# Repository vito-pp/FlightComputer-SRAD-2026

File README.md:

# FlightComputer-SRAD-2026

---

# RP2040 Firmware Build Instructions

This project uses the Raspberry Pi Pico SDK with CMake and the ARM GCC toolchain.

Follow these steps to set up the build environment.

---

## 1. Install dependencies (Linux)

On Debian/Ubuntu:

```bash
sudo apt update
sudo apt install cmake gcc-arm-none-eabi libnewlib-arm-none-eabi build-essential git
```

On Fedora:

```bash
sudo dnf install cmake arm-none-eabi-gcc-cs arm-none-eabi-newlib make git
```

Check installation:

```bash
arm-none-eabi-gcc --version
cmake --version
```

---

## 2. Download the Pico SDK

Clone the SDK somewhere on your system (outside this repo):

```bash
git clone https://github.com/raspberrypi/pico-sdk.git ~/pico-sdk
```

---

## 3. Set the SDK path environment variable

Set this variable so CMake can find the SDK:

```bash
export PICO_SDK_PATH=~/pico-sdk
```

To make it permanent (bash):

```bash
echo 'export PICO_SDK_PATH=~/pico-sdk' >> ~/.bashrc
source ~/.bashrc
```

---

## 4. Build the project

From the `code/` directory:

```bash
mkdir build
cd build
cmake ..
make -j$(nproc)
```

After building, the firmware file will be generated:

```bash
flight_computer.uf2
```

---

## 5. Flash to the RP2040

1. Hold the **BOOTSEL** button on the Pico
2. Plug the Pico into USB
3. Release BOOTSEL
4. Copy the UF2 file:

```bash
cp flight_computer.uf2 /media/$USER/RPI-RP2/
```

(The mount path may vary depending on your system.)

---

## 6. Rebuilding later

After the first build, you usually only need:

```bash
cd code/build
make -j$(nproc)
```

If you change `CMakeLists.txt`, run:

```bash
cmake ..
```

If something breaks, clean build:

```bash
cd code
rm -rf build
mkdir build
cd build
cmake ..
make -j$(nproc)
```

## Submodules / External Libraries

This project uses the SD-card library `no-OS-FatFS-SD-SDIO-SPI-RPi-Pico` as a Git submodule.

### Fresh clone

Clone with submodules:

```bash
git clone --recurse-submodules <repo-url>
```

### Existing clone

If the repository was already cloned without submodules:

```bash
git submodule update --init --recursive
```

After pulling updates:

```bash
git pull --recurse-submodules
git submodule update --init --recursive
```

### SD-card library notes

This project uses:

```text
no-OS-FatFS-SD-SDIO-SPI-RPi-Pico
```

in SDIO/PIO 4-bit mode.

The library contains a project-specific patch because the SD clock pin is routed differently on this board.

SD pin mapping:

```text
SD_CMD  -> GPIO18
SD_DAT0 -> GPIO19
SD_DAT1 -> GPIO20
SD_DAT2 -> GPIO21
SD_DAT3 -> GPIO22
SD_CLK  -> GPIO25
```

The SDIO PIO configuration was modified with:

```text
SDIO_CLK_PIN_D0_OFFSET = 6
```

The patched submodule commit must be available from the configured submodule remote.

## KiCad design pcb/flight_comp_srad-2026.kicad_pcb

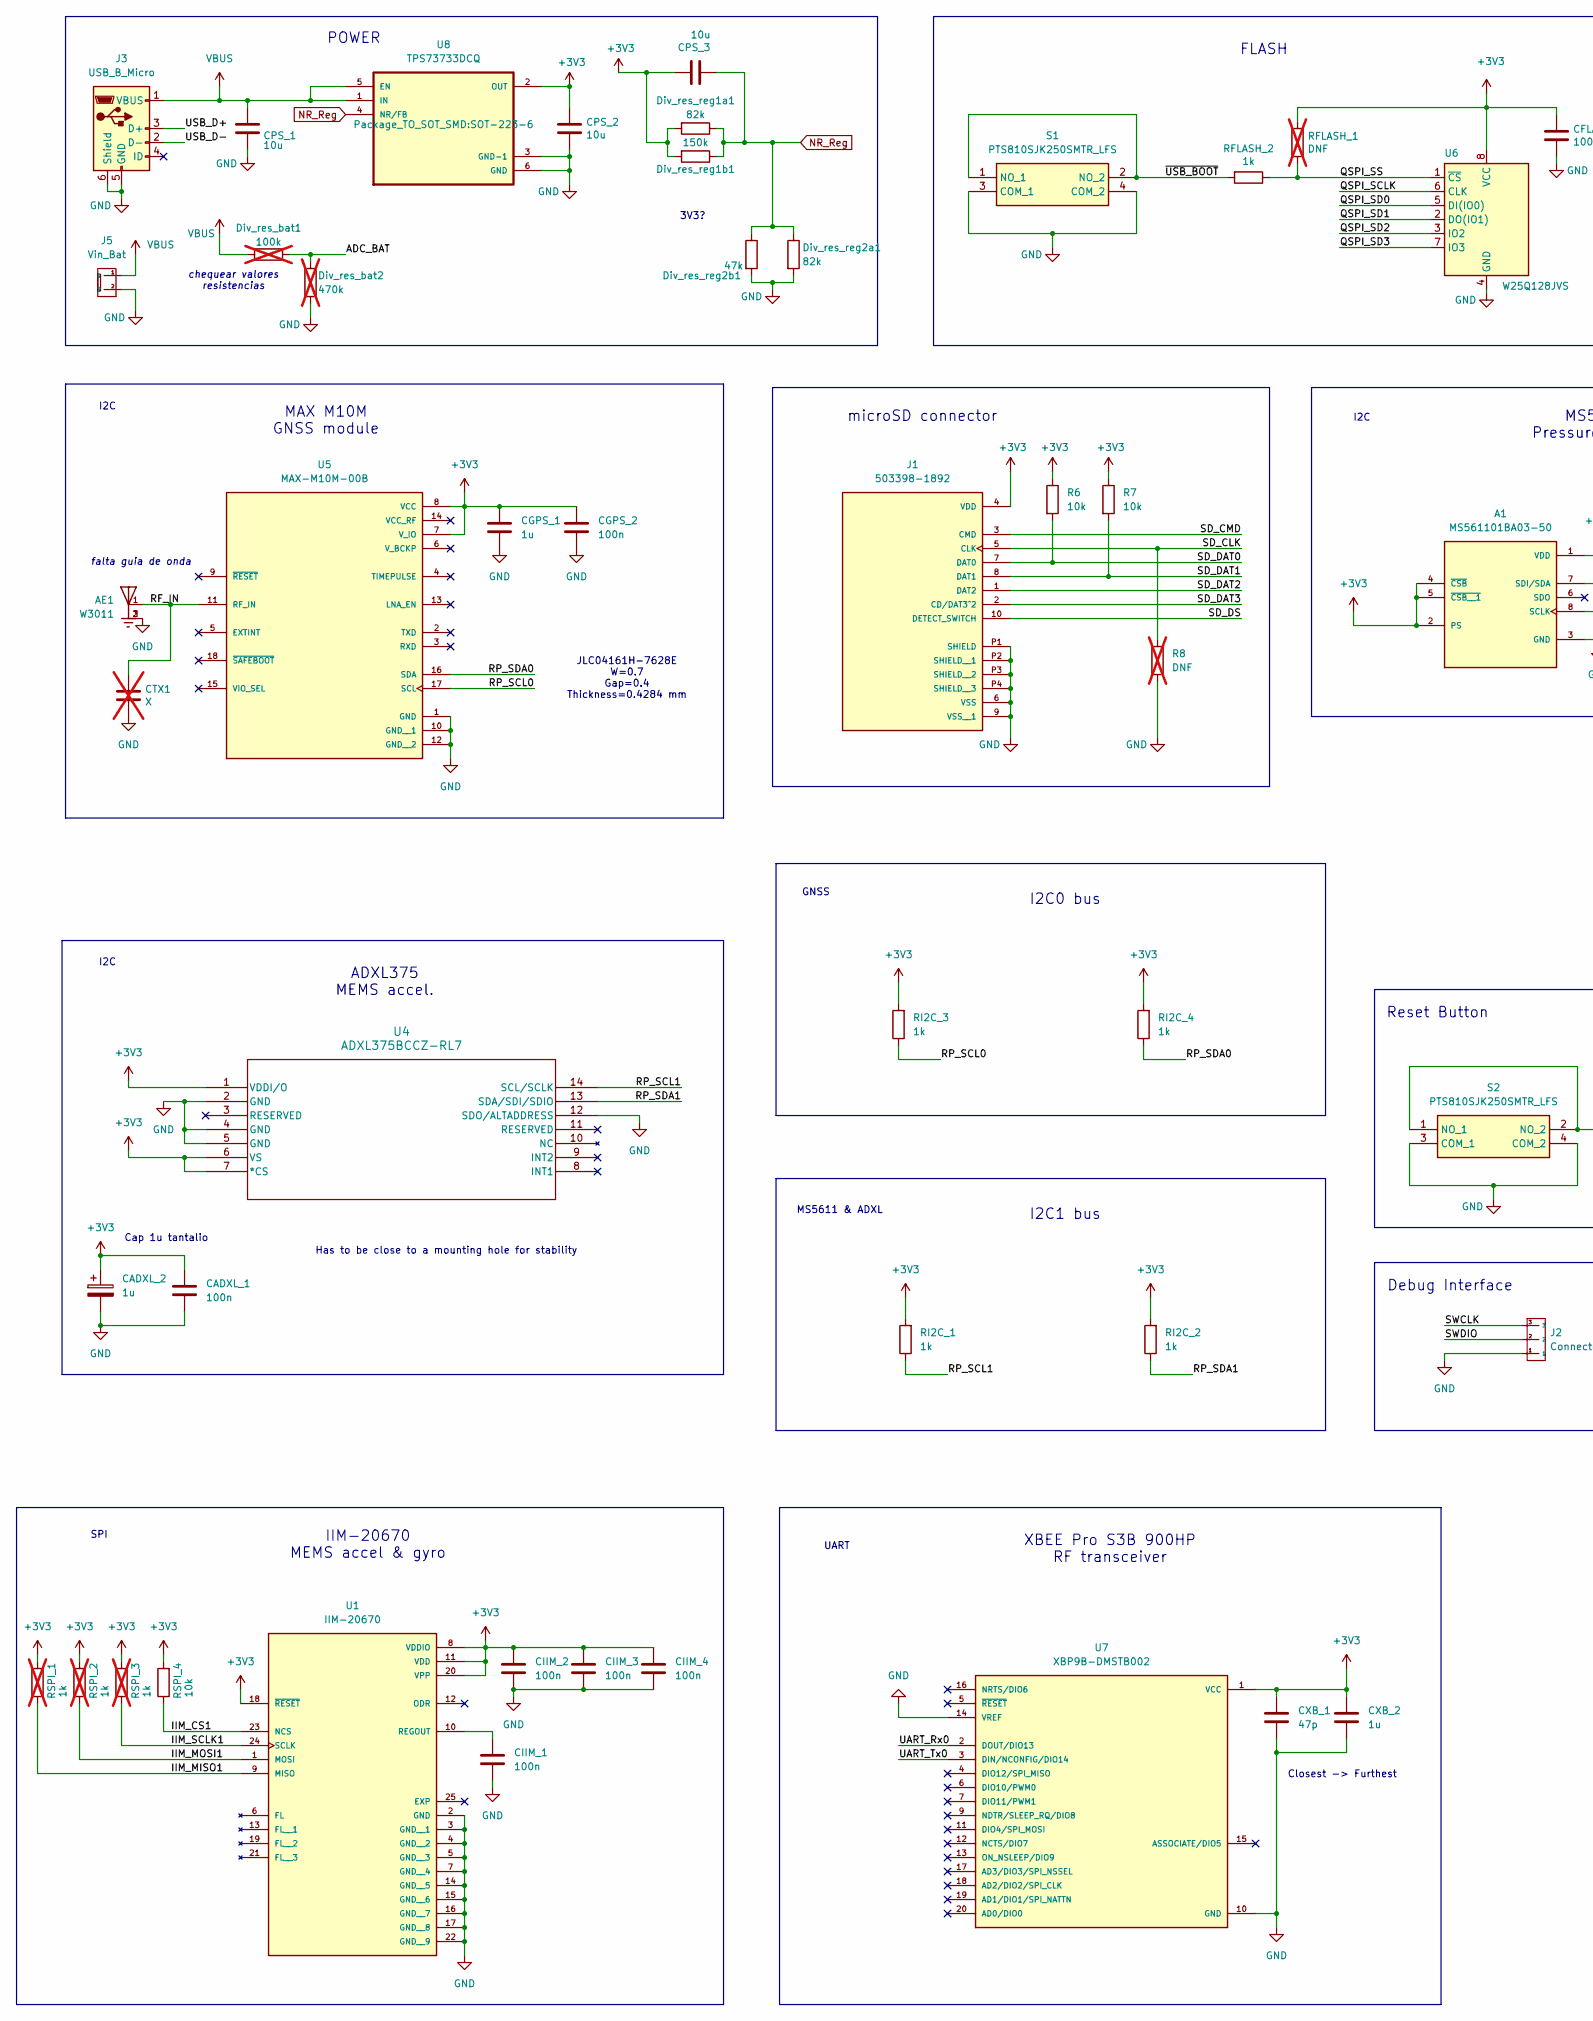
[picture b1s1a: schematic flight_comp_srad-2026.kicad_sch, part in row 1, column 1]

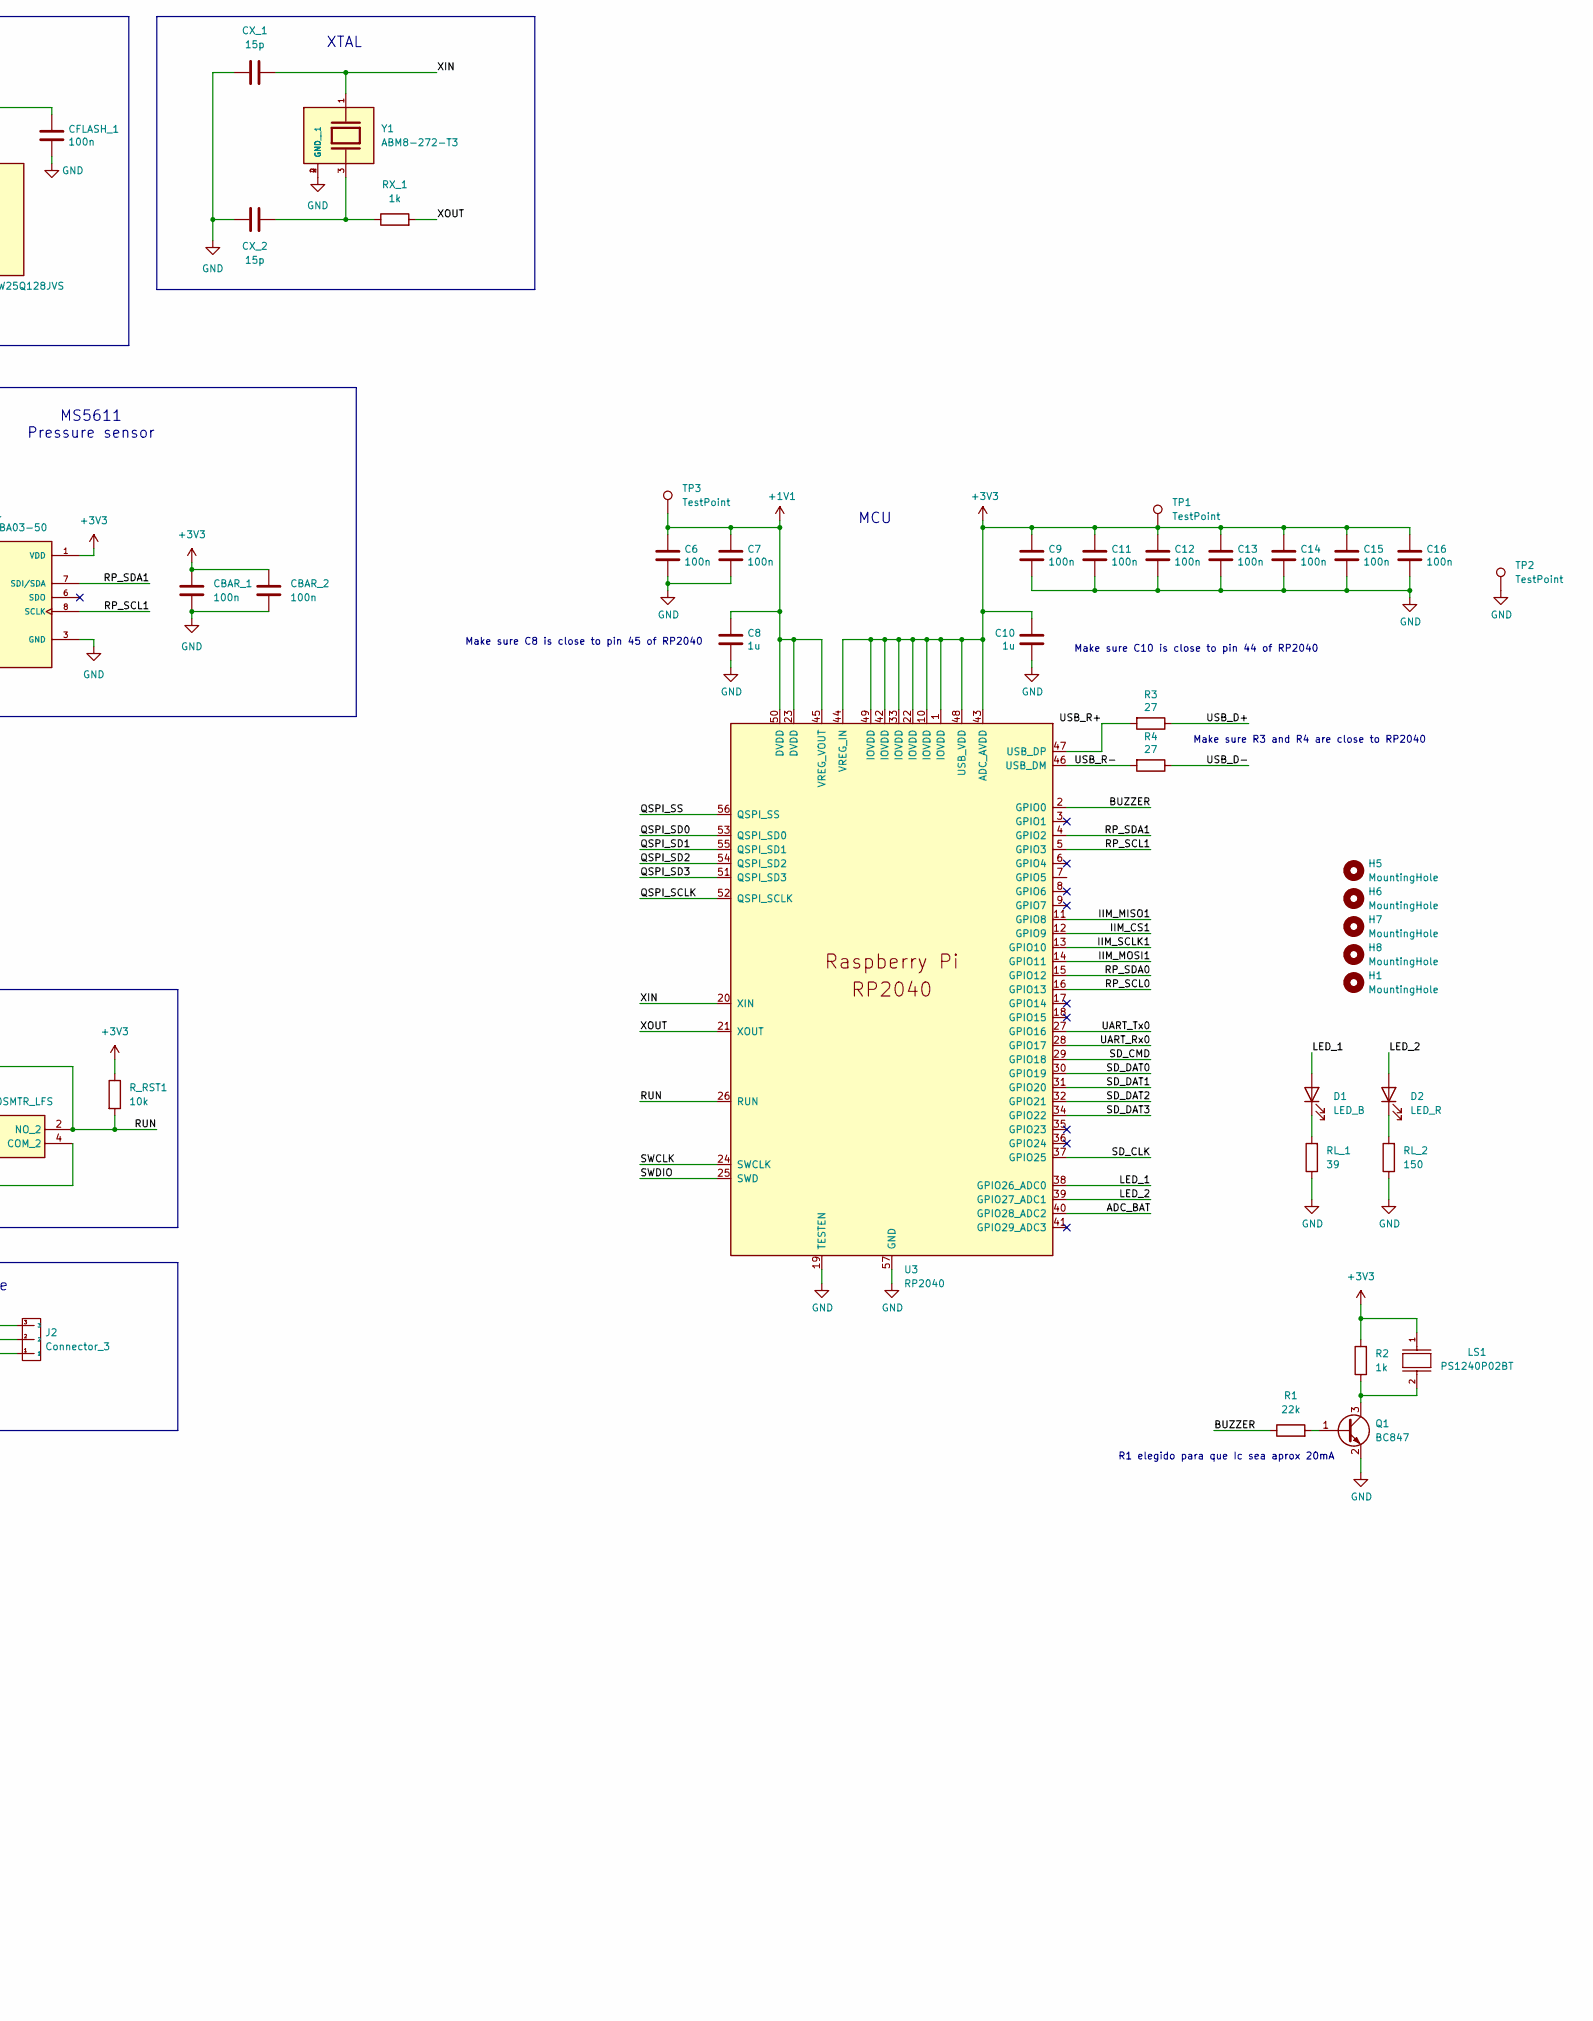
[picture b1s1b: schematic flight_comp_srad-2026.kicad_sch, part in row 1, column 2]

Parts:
A1: MS561101BA03-50; XDCR_MS561101BA03-50; PARTREV 06/2017
AE1: W3011; XDCR_W3011; PARTREV N/A
C6, C7, C9, C11, C12, C13, C14, C15, C16: 100n; C_0402_1005Metric
C8, C10: 1u; C_0402_1005Metric
CADXL_1: 100n; C_0402_1005Metric
CADXL_2: 1u; C_0805_2012Metric
CBAR_1, CBAR_2: 100n; C_0402_1005Metric
CFLASH_1: 100n; C_0402_1005Metric
CGPS_1: 1u; C_0805_2012Metric
CGPS_2: 100n; C_0603_1608Metric
CIIM_1, CIIM_2, CIIM_3, CIIM_4: 100n; C_0402_1005Metric
CPS_1, CPS_2, CPS_3: 10u; C_0805_2012Metric
CTX1: X; C_0805_2012Metric; not fitted
CXB_1: 47p; C_0805_2012Metric
CXB_2: 1u; C_0805_2012Metric
CX_1, CX_2: 15p; C_0805_2012Metric
D1: LED_B; LED_0603_1608Metric
D2: LED_R; LED_0603_1608Metric
Div_res_bat1: 100k; R_0805_2012Metric; not fitted
Div_res_bat2: 470k; R_0805_2012Metric; not fitted
Div_res_reg1a1, Div_res_reg2a1: 82k; R_0805_2012Metric
Div_res_reg1b1: 150k; R_0805_2012Metric
Div_res_reg2b1: 47k; R_0805_2012Metric
H1, H5, H6, H7, H8: MountingHole; MountingHole_3mm
J1: 503398-1892; MOLEX_503398-1892; PARTREV 0
J2: Connector_3; PinHeader_1x03_P2.54mm_Vertical
J3: USB_B_Micro; USB_Micro-B_Amphenol_10103594-0001LF_Horizontal
J5: Vin_Bat; Molex_1x02_P2.54mm
LS1: PS1240P02BT; Buzzer_TDK_PS1240P02BT_D12.2mm_H6.5mm
Q1: BC847; SOT-23
R1: 22k; R_0805_2012Metric
R2: 1k; R_0805_2012Metric
R3, R4: 27; R_0603_1608Metric
R6, R7: 10k; R_0805_2012Metric
R8: DNF; R_0805_2012Metric; not fitted
RFLASH_1: DNF; R_0805_2012Metric; not fitted
RFLASH_2: 1k; R_0805_2012Metric
RI2C_1, RI2C_2, RI2C_3, RI2C_4: 1k; R_0603_1608Metric
RL_1: 39; R_0805_2012Metric
RL_2: 150; R_0805_2012Metric
RSPI_1, RSPI_2, RSPI_3: 1k; R_0603_1608Metric; not fitted
RSPI_4: 10k; R_0603_1608Metric
RX_1: 1k; R_0805_2012Metric
R_RST1: 10k; R_0805_2012Metric
S1, S2: PTS810SJK250SMTR_LFS; PTS810SJK250SMTRLFS; Mouser Part Number 611-PTS810SJK250SMTR
TP1, TP2, TP3: TestPoint; TestPoint_Pad_D1.0mm
U1: IIM-20670; QFN50P450X450X115-25N; PARTREV 1.1
U3: RP2040; QFN-56-1EP_7x7mm_P0.4mm_EP3.2x3.2mm_ThermalVias
U4: ADXL375BCCZ-RL7; LGA-14_3x5mm_P0.8mm_LayoutBorder1x6y
U5: MAX-M10M-00B; XCVR_MAX-M10M-00B; PARTREV C1
U6: W25Q128JVS; SOIC-8_5.3x5.3mm_P1.27mm
U7: XBP9B-DMSTB002; XBEEPRO
U8: TPS73733DCQ; SOT-223-6
Y1: ABM8-272-T3; XTAL_ABM8-272-T3; PARTREV 07-29-20

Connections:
+1V1: C6.1, C7.1, C8.1, TP3.1, U3.23 (DVDD), U3.45 (VREG_VOUT), U3.50 (DVDD)
+3V3: A1.1 (VDD), A1.2 (PS), A1.4 (~CSB), A1.5 (~CSB__1), C9.1, C10.1, C11.1, C12.1, C13.1, C14.1, C15.1, C16.1, CADXL_1.1, CADXL_2.1, CBAR_1.1, CBAR_2.1, CFLASH_1.1, CGPS_1.1, CGPS_2.1, CIIM_2.1, CIIM_3.1, CIIM_4.1, CPS_2.1, CPS_3.1, CXB_1.1, CXB_2.1, Div_res_reg1a1.2, Div_res_reg1b1.2, J1.4 (VDD), LS1.1, R2.2, R6.1, R7.1, RFLASH_1.1, RI2C_1.2, RI2C_2.2, RI2C_3.2, RI2C_4.2, RSPI_1.2, RSPI_2.2, RSPI_3.2, RSPI_4.2, R_RST1.1, TP1.1, U1.8 (VDDIO), U1.11 (VDD), U1.18 (~RESET), U1.20 (VPP), U3.1 (IOVDD), U3.10 (IOVDD), U3.22 (IOVDD), U3.33 (IOVDD), U3.42 (IOVDD), U3.43 (ADC_AVDD), U3.44 (VREG_IN), U3.48 (USB_VDD), U3.49 (IOVDD), U4.1 (VDDI/O), U4.6 (VS), U4.7 (*CS), U5.7 (V_IO), U5.8 (VCC), U6.8 (VCC), U7.1 (VCC), U8.2 (OUT)
/ADC_BAT: Div_res_bat1.1, Div_res_bat2.1, U3.40 (GPIO28_ADC2)
/BUZZER: R1.1, U3.2 (GPIO0)
/IIM_CS1: RSPI_4.1, U1.23 (NCS), U3.12 (GPIO9)
/IIM_MISO1: RSPI_1.1, U1.9 (MISO), U3.11 (GPIO8)
/IIM_MOSI1: RSPI_2.1, U1.1 (MOSI), U3.14 (GPIO11)
/IIM_SCLK1: RSPI_3.1, U1.24 (SCLK), U3.13 (GPIO10)
/LED_1: D1.2 (A), U3.38 (GPIO26_ADC0)
/LED_2: D2.2 (A), U3.39 (GPIO27_ADC1)
/QSPI_SCLK: U3.52 (QSPI_SCLK), U6.6 (CLK)
/QSPI_SD0: U3.53 (QSPI_SD0), U6.5 (DI(IO0))
/QSPI_SD1: U3.55 (QSPI_SD1), U6.2 (DO(IO1))
/QSPI_SD2: U3.54 (QSPI_SD2), U6.3 (IO2)
/QSPI_SD3: U3.51 (QSPI_SD3), U6.7 (IO3)
/QSPI_SS: RFLASH_1.2, RFLASH_2.1, U3.56 (QSPI_SS), U6.1 (~CS)
/RF_IN: AE1.1, CTX1.1, U5.11 (RF_IN)
/RP_SCL0: RI2C_3.1, U3.16 (GPIO13), U5.17 (SCL)
/RP_SCL1: A1.8 (SCLK), RI2C_1.1, U3.5 (GPIO3), U4.14 (SCL/SCLK)
/RP_SDA0: RI2C_4.1, U3.15 (GPIO12), U5.16 (SDA)
/RP_SDA1: A1.7 (SDI/SDA), RI2C_2.1, U3.4 (GPIO2), U4.13 (SDA/SDI/SDIO)
/RUN: R_RST1.2, S2.1 (NO_1), S2.2 (NO_2), U3.26 (RUN)
/SD_CLK: J1.5 (CLK), R8.1, U3.37 (GPIO25)
/SD_CMD: J1.3 (CMD), U3.29 (GPIO18)
/SD_DAT0: J1.7 (DAT0), R6.2, U3.30 (GPIO19)
/SD_DAT1: J1.8 (DAT1), R7.2, U3.31 (GPIO20)
/SD_DAT2: J1.1 (DAT2), U3.32 (GPIO21)
/SD_DAT3: J1.2 (CD/DAT3^2), U3.34 (GPIO22)
/SD_DS: J1.10 (DETECT_SWITCH)
/SWCLK: J2.3, U3.24 (SWCLK)
/SWDIO: J2.2, U3.25 (SWD)
/UART_Rx0: U3.28 (GPIO17), U7.2 (DOUT/DIO13)
/UART_Tx0: U3.27 (GPIO16), U7.3 (DIN/NCONFIG/DIO14)
/USB_D+: J3.3 (D+), R3.1
/USB_D-: J3.2 (D-), R4.1
/USB_R+: R3.2, U3.47 (USB_DP)
/USB_R-: R4.2, U3.46 (USB_DM)
/XIN: CX_1.2, U3.20 (XIN), Y1.1
/XOUT: RX_1.2, U3.21 (XOUT)
/~USB_BOOT: RFLASH_2.2, S1.1 (NO_1), S1.2 (NO_2)
GND: A1.3 (GND), AE1.2, AE1.3, C6.2, C7.2, C8.2, C9.2, C10.2, C11.2, C12.2, C13.2, C14.2, C15.2, C16.2, CADXL_1.2, CADXL_2.2, CBAR_1.2, CBAR_2.2, CFLASH_1.2, CGPS_1.2, CGPS_2.2, CIIM_1.2, CIIM_2.2, CIIM_3.2, CIIM_4.2, CPS_1.2, CPS_2.2, CTX1.2, CXB_1.2, CXB_2.2, CX_1.1, CX_2.1, Div_res_bat2.2, Div_res_reg2a1.2, Div_res_reg2b1.2, J1.6 (VSS), J1.9 (VSS__1), J1.P1 (SHIELD), J1.P2 (SHIELD__1), J1.P3 (SHIELD__2), J1.P4 (SHIELD__3), J2.1, J3.5 (GND), J3.6 (Shield), J5.2, Q1.2 (E), R8.2, RL_1.1, RL_2.1, S1.3 (COM_1), S1.4 (COM_2), S2.3 (COM_1), S2.4 (COM_2), TP2.1, U1.2 (GND), U1.3 (GND__1), U1.4 (GND__2), U1.5 (GND__3), U1.7 (GND__4), U1.14 (GND__5), U1.15 (GND__6), U1.16 (GND__7), U1.17 (GND__8), U1.22 (GND__9), U3.19 (TESTEN), U3.57 (GND), U4.2 (GND), U4.4 (GND), U4.5 (GND), U4.12 (SDO/ALTADDRESS), U5.1 (GND), U5.10 (GND__1), U5.12 (GND__2), U6.4 (GND), U7.10 (GND), U7.14 (VREF), U8.3 (GND-1), U8.6 (GND), Y1.2 (GND), Y1.4 (GND__1)
NR_Reg: CPS_3.2, Div_res_reg1a1.1, Div_res_reg1b1.1, Div_res_reg2a1.1, Div_res_reg2b1.1, U8.4 (NR/FB)
unnamed: CX_2.2, RX_1.1, Y1.3
unnamed: D1.1 (K), RL_1.2
unnamed: D2.1 (K), RL_2.2
unnamed: Q1.1 (B), R1.2
unnamed: LS1.2, Q1.3 (C), R2.1
unnamed: CIIM_1.1, U1.10 (REGOUT)
VBUS: CPS_1.1, Div_res_bat1.2, J3.1 (VBUS), J5.1, U8.1 (IN), U8.5 (EN)

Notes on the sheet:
ADXL375 MEMS accel.
microSD connector
MAX M10M GNSS module
Make sure C8 is close to pin 45 of RP2040
MS5611 Pressure sensor
I2C
IIM-20670 MEMS accel & gyro
Reset Button
MCU
GNSS
chequear valores resistencias
falta guia de onda
I2C1 bus
Closest -> Furthest
3V3?
JLC04161H-7628E W=0.7 Gap=0.4 Thickness=0.4284 mm
I2C0 bus
SPI
Make sure C10 is close to pin 44 of RP2040
XBEE Pro S3B 900HP RF transceiver
Debug Interface
FLASH
Has to be close to a mounting hole for stability
Cap 1u tantalio
UART
MS5611 & ADXL
Make sure R3 and R4 are close to RP2040
R1 elegido para que Ic sea aprox 20mA
XTAL
POWER

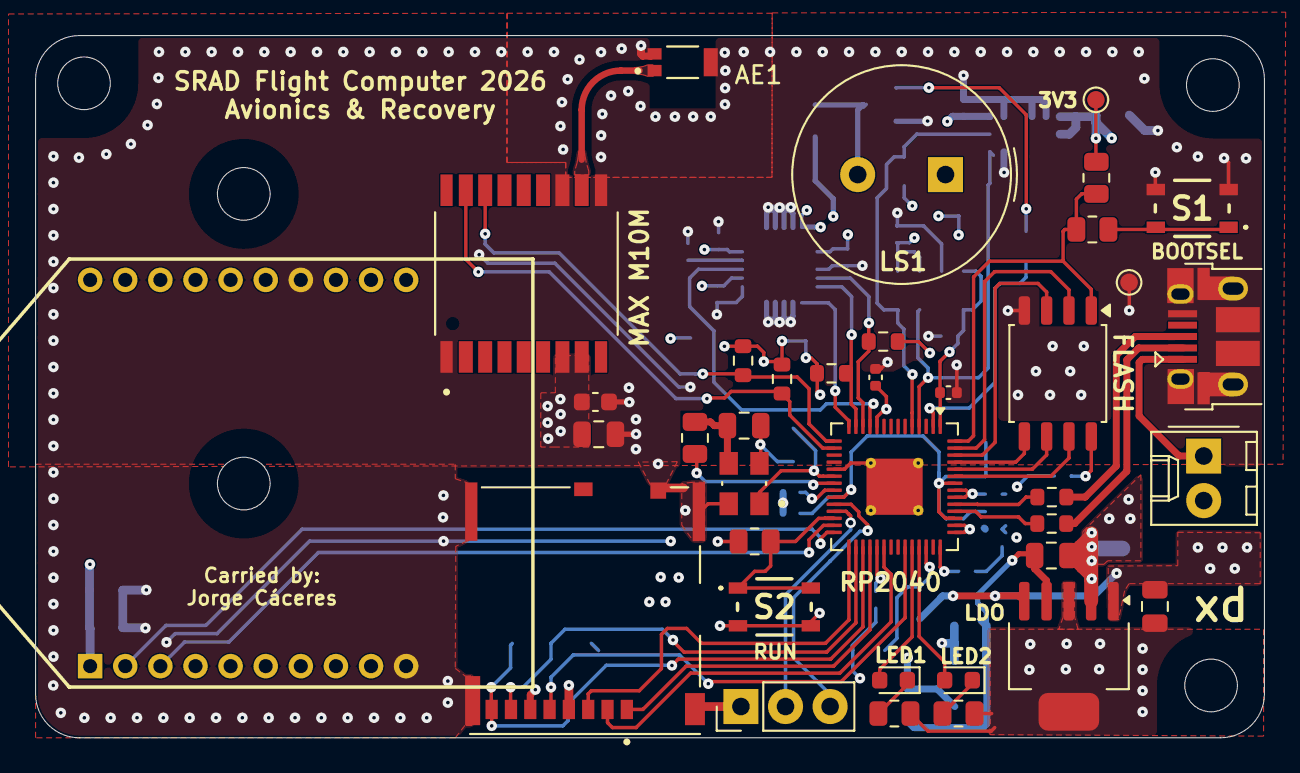
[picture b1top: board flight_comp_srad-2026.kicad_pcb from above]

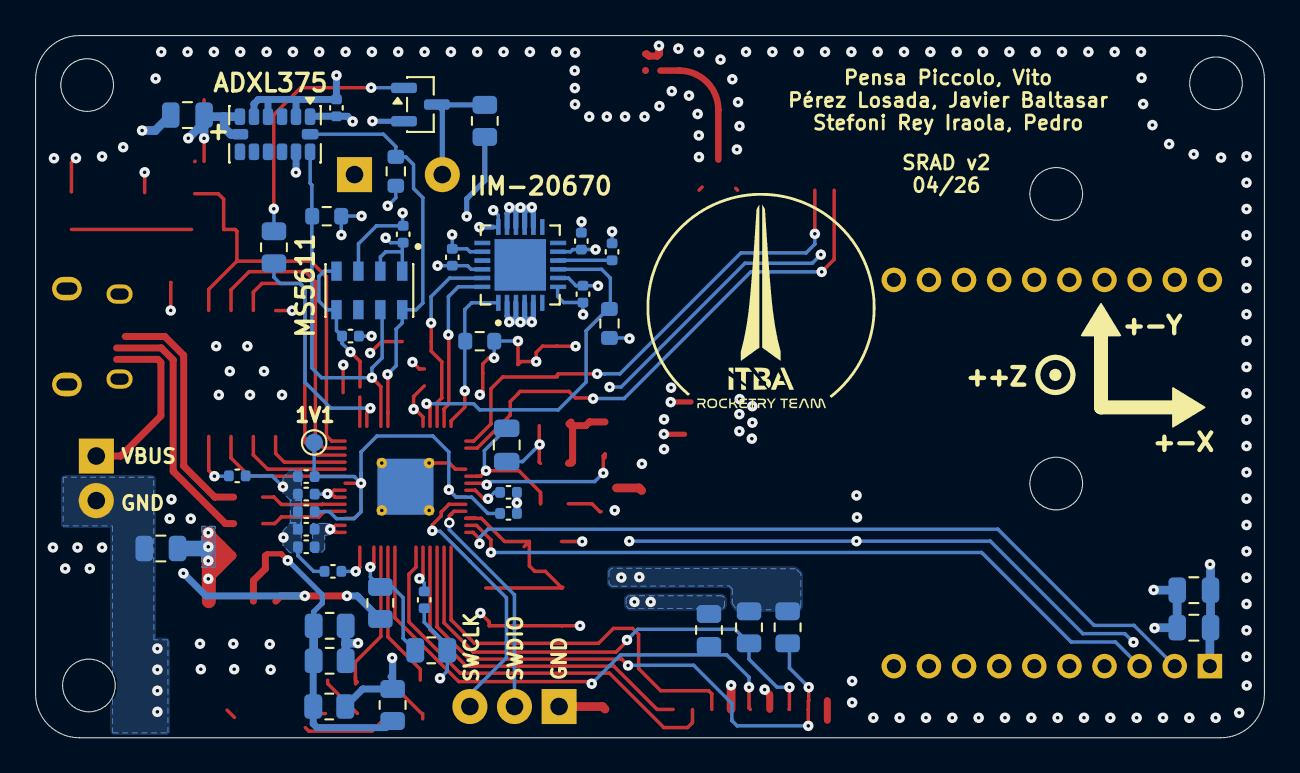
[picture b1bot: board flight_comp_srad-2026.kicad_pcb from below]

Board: 4 copper layers, 70.0 x 40.0 mm, 84 parts (42 on the bottom side), 48 nets.

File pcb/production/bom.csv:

Designator,Footprint,Quantity,Value,LCSC Part #
A1,XDCR_MS561101BA03-50,1,MS561101BA03-50,
AE1,XDCR_W3011,1,W3011,
"C10, C8",0402,2,1u,
"C11, C12, C13, C14, C15, C16, C6, C7, C9, CADXL_1, CBAR_1, CBAR_2, CFLASH_1, CIIM_1, CIIM_2, CIIM_3, CIIM_4",0402,17,100n,
"CADXL_2, CGPS_1, CXB_2",0805,3,1u,
CGPS_2,0603,1,100n,
"CPS_1, CPS_2, CPS_3",0805,3,10u,
CXB_1,0805,1,47p,
"CX_1, CX_2",0805,2,15p,
D1,0603,1,LED_B,
D2,0603,1,LED_R,
"DIV_RES_REG1A1, DIV_RES_REG2A1",0805,2,82k,
DIV_RES_REG1B1,0805,1,150k,
DIV_RES_REG2B1,0805,1,47k,
J1,MOLEX_503398-1892,1,503398-1892,
J2,PinHeader_1x03_P2.54mm_Vertical,1,Connector_3,
J3,USB_Micro-B_Amphenol_10103594-0001LF_Horizontal,1,USB_B_Micro,
J5,Molex_1x02_P2.54mm,1,Vin_Bat,
LS1,Buzzer_TDK_PS1240P02BT_D12.2mm_H6.5mm,1,PS1240P02BT,
Q1,SOT-23,1,BC847,
R1,0805,1,22k,
"R2, RFLASH_2, RX_1",0805,3,1k,
"R3, R4",0603,2,27,
"R6, R7, R_RST1",0805,3,10k,
"RI2C_1, RI2C_2, RI2C_3, RI2C_4",0603,4,1k,
RL_1,0805,1,39,
RL_2,0805,1,150,
RSPI_4,0603,1,10k,
"S1, S2",PTS810SJK250SMTRLFS,2,PTS810SJK250SMTR_LFS,
"TP1, TP2, TP3",TestPoint_Pad_D1.0mm,3,TestPoint,
U1,QFN50P450X450X115-25N,1,IIM-20670,
U3,QFN-56-1EP_7x7mm_P0.4mm_EP3.2x3.2mm_ThermalVias,1,RP2040,
U4,LGA-14_3x5mm_P0.8mm_LayoutBorder1x6y,1,ADXL375BCCZ-RL7,
U5,XCVR_MAX-M10M-00B,1,MAX-M10M-00B,
U6,SOIC-8_5.3x5.3mm_P1.27mm,1,W25Q128JVS,
U7,XBEEPRO,1,XBP9B-DMSTB002,
U8,SOT-223-6,1,TPS73733DCQ,
Y1,XTAL_ABM8-272-T3,1,ABM8-272-T3,

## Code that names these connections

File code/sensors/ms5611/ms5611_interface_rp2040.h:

/**
 * @file      ms5611_interface_rp2040.h
 * @brief     MS5611 RP2040 Pico SDK platform interface header
 * @version   1.0.0
 * @date      2026-04-02
 *
 * @details   Platform-specific interface implementation for driving the MS5611
 *            barometric pressure sensor via I2C on an RP2040-based SRAD flight
 *            computer. Implements the callback functions required by the
 *            LibDriver MS5611 library.
 *
 *            Hardware wiring (SRAD 2026 Flight Computer):
 *              - I2C Bus 1: SDA = GPIO2  (RP_SDA1), SCL = GPIO3  (RP_SCL1)
 *                Shared bus with ADXL375. GNSS is on I2C0 (GPIO 12/13).
 *              - MS5611 CSB pin determines I2C address:
 *                  CSB = GND → 0x77 (LibDriver: 0xEE)
 *                  CSB = VDD → 0x76 (LibDriver: 0xEC)
 *
 * @note      This file only implements I2C (not SPI) since the MS5611 is
 *            connected via I2C on the SRAD 2026 PCB. SPI stubs are provided
 *            to satisfy the LibDriver link macros.
 */

#ifndef MS5611_INTERFACE_RP2040_H
#define MS5611_INTERFACE_RP2040_H

#include "driver_ms5611.h"
#include "hardware/i2c.h"

#ifdef __cplusplus
extern "C" {
#endif

/* =========================================================================
 * HARDWARE CONFIGURATION — ADJUST THESE TO MATCH YOUR PCB
 * ========================================================================= */

/**
 * @brief Which I2C peripheral to use.
 *        i2c1 → GPIO 2/3   (RP_SDA1 / RP_SCL1) — MS5611 + ADXL375
 *        i2c0 → GPIO 12/13 (RP_SDA0 / RP_SCL0) — GNSS MAX-M10M only
 *
 *        The MS5611 is on I2C1 on the SRAD 2026 PCB.
 */
#ifndef MS5611_I2C_INSTANCE
#define MS5611_I2C_INSTANCE     i2c1
#endif

/**
 * @brief I2C bus frequency in Hz.
 *        400 kHz (Fast Mode) is recommended and supported by the MS5611.
 */
#ifndef MS5611_I2C_FREQ_HZ
#define MS5611_I2C_FREQ_HZ      (400 * 1000)
#endif

/**
 * @brief GPIO pin numbers for SDA and SCL.
 *        Must match the I2C instance selected above.
 *        i2c1 → SDA=2  (RP_SDA1), SCL=3  (RP_SCL1)
 *        i2c0 → SDA=12 (RP_SDA0), SCL=13 (RP_SCL0)
 */
#ifndef MS5611_I2C_SDA_PIN
#define MS5611_I2C_SDA_PIN      2
#endif

#ifndef MS5611_I2C_SCL_PIN
#define MS5611_I2C_SCL_PIN      3
#endif

/**
 * @brief I2C timeout in microseconds for blocking operations.
 *        50 ms is generous — the longest MS5611 conversion is ~9.04 ms.
 */
#ifndef MS5611_I2C_TIMEOUT_US
#define MS5611_I2C_TIMEOUT_US   (50 * 1000)
#endif

/* =========================================================================
 * INTERFACE FUNCTIONS — plug into LibDriver via LINK macros
 * ========================================================================= */

/**
 * @brief  Initialize the I2C bus for MS5611 communication.
 * @return 0 on success, 1 on failure.
 * @note   Initializes the I2C peripheral, sets GPIO functions, and enables
 *         internal pull-ups. If the bus is already initialized elsewhere
 *         (e.g. shared with BMP280), you may wish to make this a no-op and
 *         handle initialization in main.
 */
uint8_t ms5611_interface_iic_init(void);

/**
 * @brief  Deinitialize the I2C bus.
 * @return 0 on success, 1 on failure.
 * @note   Be careful on a shared bus — deinitializing will affect all devices.
 */
uint8_t ms5611_interface_iic_deinit(void);

/**
 * @brief      Read data from the MS5611 via I2C.
 * @param[in]  addr  8-bit I2C write address (LibDriver convention, e.g. 0xEE).
 * @param[in]  reg   Command/register byte to send before reading.
 * @param[out] buf   Buffer to store the received bytes.
 * @param[in]  len   Number of bytes to read.
 * @return     0 on success, 1 on failure.
 *
 * @note  The MS5611 protocol for I2C reads:
 *        1. Write the command byte (reg) to the device.
 *        2. Read len bytes from the device.
 *        LibDriver passes 8-bit addresses; Pico SDK uses 7-bit internally.
 */
uint8_t ms5611_interface_iic_read(uint8_t addr, uint8_t reg, uint8_t *buf, uint16_t len);

/**
 * @brief     Write data to the MS5611 via I2C.
 * @param[in] addr  8-bit I2C write address (LibDriver convention).
 * @param[in] reg   Command byte to send.
 * @param[in] buf   Pointer to data bytes to send after the command (can be NULL).
 * @param[in] len   Number of data bytes (can be 0 for command-only writes).
 * @return    0 on success, 1 on failure.
 *
 * @note  For the MS5611, most writes are command-only (len=0): Reset, Convert, etc.
 *        The function sends [reg] followed by [buf[0..len-1]] in a single transaction.
 */
uint8_t ms5611_interface_iic_write(uint8_t addr, uint8_t reg, uint8_t *buf, uint16_t len);

/**
 * @brief  SPI init stub (not used — MS5611 is on I2C on this board).
 * @return Always 0.
 */
uint8_t ms5611_interface_spi_init(void);

/**
 * @brief  SPI deinit stub.
 * @return Always 0.
 */
uint8_t ms5611_interface_spi_deinit(void);

/**
 * @brief  SPI read stub.
 * @return Always 0.
 */
uint8_t ms5611_interface_spi_read(uint8_t reg, uint8_t *buf, uint16_t len);

/**
 * @brief  SPI write stub.
 * @return Always 0.
 */
uint8_t ms5611_interface_spi_write(uint8_t reg, uint8_t *buf, uint16_t len);

/**
 * @brief     Delay for the specified number of milliseconds.
 * @param[in] ms  Delay time in milliseconds.
 */
void ms5611_interface_delay_ms(uint32_t ms);

/**
 * @brief     Print a debug message via USB/UART stdio.
 * @param[in] fmt  printf-style format string.
 */
void ms5611_interface_debug_print(const char *const fmt, ...);

#ifdef __cplusplus
}
#endif

#endif /* MS5611_INTERFACE_RP2040_H */

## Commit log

2025-10-07 first commit :^D
2025-10-13 agregue datasheets y puse pines para el xbee
2025-10-27 added new imu's
2025-10-27 added adx 3d model
2025-10-27 added xtal
2025-11-03 agregue datasheets nuevo gyro
2025-11-03 mas cosas al schem
2025-11-03 update gitignore
2025-11-03 agregue datasheets regulador y flash mem
2025-11-20 nuevos componentes menos xtal
2025-11-20 xtal smd
2025-12-04 agregue xbee footprint, symb y .step
2025-12-05 todos los IC menos XBEE
2025-12-05 schematic del rp2040 hecho
2025-12-06 RP2040 listo, faltan sensores y comms
2025-12-06 added datasheets and components
2025-12-06 updated datasheets for xbee
2025-12-06 cosas del xbee
2025-12-07 footprints y cosas
2025-12-09 queda cablear los gpios
2025-12-10 plano de masa y antena puestos
2025-12-14 conectado spi del iim y ruteo de algunos caps de desacople
2025-12-17 listo los caps de desacople de la rp2040
2025-12-17 listo el routeo de casi todo falta layer gnd y 3v3, capas adxl
2025-12-26 Planos de 3V3 y VBUS, y otras cositas
    Planos de 3V3 y VBUS, y otras cositas
2025-12-29 2 LEDs are back, ruteo pistas SD y pistas bananeras de 3V3 y GND
2026-01-02 Pistas terminadas (FALTA REVISAR) + medidor tensión batería
2026-01-02 Pistas terminadas (FALTA REVISAR) + medidor tensión batería
    Me faltó poner una pista más xd
2026-01-04 routeo listo, falta revisar las conecc
2026-01-04 agregue coments
2026-01-07 Cambio plano 3v3
2026-01-12 linea de transmision ruteada
2026-02-01 Update flight_comp_srad-2026.kicad_pcb
    1ra versión serigrafía
2026-02-04 Cambio de regulador de tensión - chequear impedancia de línea
2026-02-04 SCHK de lo anterior - cambio en reg de tension
    me olvide de guardar el esquematico antes de pushear lo anterior
2026-02-10 Realimentación bien hecha y agujeros ajustados
2026-02-10 Final?
    Can you beat KiCAD with dementia?
2026-02-10 cambio P-UPs y BOOT a 0805
2026-02-10 agregue beeper que falta conectar, saque vias abajo de pads y saque la filling zone gnd del bottom del regulador
2026-02-10 beeper listo
2026-02-10 beeper listo listo
2026-02-18 quedan 62 errores de DRC mas warnings
    principales errores:
    - clearance violation (no sé por qué está en 0.2mm pero no puedo cambiarlo XD)
    - cortos por las vias más grandes
    - boludeces de la serigrafía, habría que volar todo lo que no sea importante
    - falta poner shunt a la linea de tx, no se como porque no entra XD
    - más boludeces como la posición del USB, está bien que sobresalga (ver capa user drawings) pero da error
2026-02-18 Adición buzzer y corrección de algunos errores
2026-02-19 quedan 5 errores
    creo que todos los errores son inevitables por el diseño. quedan cosas tipo ancho del texto, pero debería salir bien todo lo importante en JLC
2026-02-22 srad versión final ahora sí 2.0 intento 17
    nigga
2026-02-22 bruh
2026-02-22 bruhbruh
2026-03-27 rp2040 toolchain set up. gitignore updated
2026-03-29 added code readme
2026-03-31 blinky working
2026-04-03 Añadido codigos MS5611
2026-04-11 PARECE terminado
2026-04-11 version final?
    uwu
2026-04-11 versión final ahora sí
    OwO
2026-05-03 https://drive.google.com/drive/folders/1AIpmniXnHx3TK0_vEmsLqZfZEH8VMv5M
2026-05-03 blink led azul anda en la placa v2
2026-05-04 added library+drvs for SD card, vibe coded main test for writing on SD
2026-05-04 reads the number stored on the SD and add 1
2026-05-06 sd logger API working, and updated main readme
2026-05-06 cleaned unused kicad dirs and files
2026-05-06 deleted unused and renamed datasheets
2026-05-06 changed directories scrtucture and adxl hal working
2026-05-07 changed directories structure inside src/
2026-05-07 testing iim drv, not working for now
2026-05-08 iim driver working
2026-05-10 buzzer working
2026-05-10 iim fully working, but temp readings are still a little off
2026-05-15 deleted sensores_test
2026-05-15 updated gitignore bc of new kicad version control files
2026-05-15 removed .history form git cache
2026-05-15 ms5611 drvs working
2026-05-15 calibrated altitude now implemented
2026-05-15 boludeces
2026-05-17 cleaner APIs for sensors. also noticed pressure readings have little drift
2026-05-18 all sensor drvs work together, and calibration forces (0,0,0) on acceleration so the readings are incremental and not absolute
2026-05-19 changed PIN --> GPIO macros
2026-05-20 added scheduling for sensors readings and ring buffer
2026-05-20 fixed bug on iim calibration
2026-05-20 cleaner main.c
2026-05-20 used the error_handler in main
2026-05-20 multicore working
2026-05-20 log onto sd on core1 working
2026-05-20 aligned adxl and iim axes
2026-05-20 removed overhead from sensor_frame_t
2026-05-20 adxl calibrated and matches readings with iim beautifully *chef's kiss*
2026-05-20 removed all printf's from non main code, and formated all files for uniform indentation
2026-05-22 xbee driver
2026-05-23 added datasheet from regulator we're using
2026-05-28 telemetry frame specified
2026-05-29 corrected the telemetry_frame and added __attribute((packed))__ to every sensor struct
2026-05-29 updated sd functions for newer frame, log workign now
2026-05-29 gnss drv compiles and removed reserved field
2026-05-29 de baja el gps
2026-05-29 added buzzer at the start
2026-05-29 changed directories for /include/drvs
2026-05-29 battery measure working
2026-05-30 blue led indicates init
2026-05-31 changed crc.c --> crc_app.c
2026-06-03 ready for flight
2026-06-03 frame freq now 100Hz
2026-06-05 bug fix in adxl calibration
